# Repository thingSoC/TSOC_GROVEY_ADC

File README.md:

# TSOC_GROVEY_ADC - thingSoC ADS1115/ADS1015 ADC Module :

**TSOC_GROVEY_ADC** is a four(4) port Analog-to-Digital converter board, an Embedded Module for thingSoC.

The **TSOC_GROVEY_ADC** can operate at either 3.3V or 5V, and can also level translate 3.3V processor bus to 5V Analog peripherals when needed.

The **TSOC_GROVEY_ADC** allows you to connect [thingSoC](http://thingsoc.github.io/), [Mikrobus](http://www.mikroe.com/mikrobus/), 
and/or [Grove System](http://www.seeedstudio.com/blog/2016/03/09/tutorial-intro-to-grove-connectors-for-arduinoraspberry-pi-projects/) 
Modules all at the same time, with any processor module.
This gives you maximum flexiblity for sensor and actuator selection, and reuse. 
When populated with the ADS1115 device it provides 16 bit ADC conversion, and when populated with the ADS1015 device provides 12 bit ADC conversion.

The thingSoC "Grovey Series" was designed as "Everyday Electronics", a no-frills, low cost, approach to modular embedded product design.
thingSoC boards are similar in size to most break-out-boards (BOBs), but feature a standardized stacking pinout, as well as an I2C metadata store (EEPROM)
to indicate what peripherals are installed.

[TSOC_GROVEY_ADC](https://github.com/thingSoC/TSOC_GROVEY_ADC)

---------------------------------------

## TSOC_GROVEY_ADC Status <a name="TSOC_GROVEY_ADC_status"/>

**11/06/2016:** 
Revision 1.0 - Initial Layout released to OSHpark

**01/10/2017:**
Revison 2.0 - released to OSHpark

---------------------------------------
## TSOC_GROVEY_ADC Model Images

[TSOC_GROVEY_ADC](https://github.com/thingSoC/TSOC_GROVEY_ADC)

[TSOC_GROVEY_ADC](https://github.com/thingSoC/TSOC_GROVEY_ADC)

---------------------------------------

## TSOC_GROVEY_ADC Documentation Index <a name="TSOC_GROVEY_ADC_documentation_index"/>

[TSOC_GROVEY_ADC Project](http://thingsoc.github.io/projects/TSOC_GROVEY_ADC.html)

[TSOC_GROVEY_ADC Hardware](https://github.com/thingSoC/TSOC_GROVEY_ADC/tree/master/TSOC_GROVEY_ADC/hardware)

---------------------------------------

## thingSoC Documentation Index <a name="thingSoC_documentation_index"/>

[thingSoC Organization Website](http://thingSoC.github.io)

[thingSoC FAQ - Frequently Asked Questions](http://thingsoc.github.io/support/faq.html)

---------------------------------------

[ 
*thingSoC*](http://thingsoc.github.io)

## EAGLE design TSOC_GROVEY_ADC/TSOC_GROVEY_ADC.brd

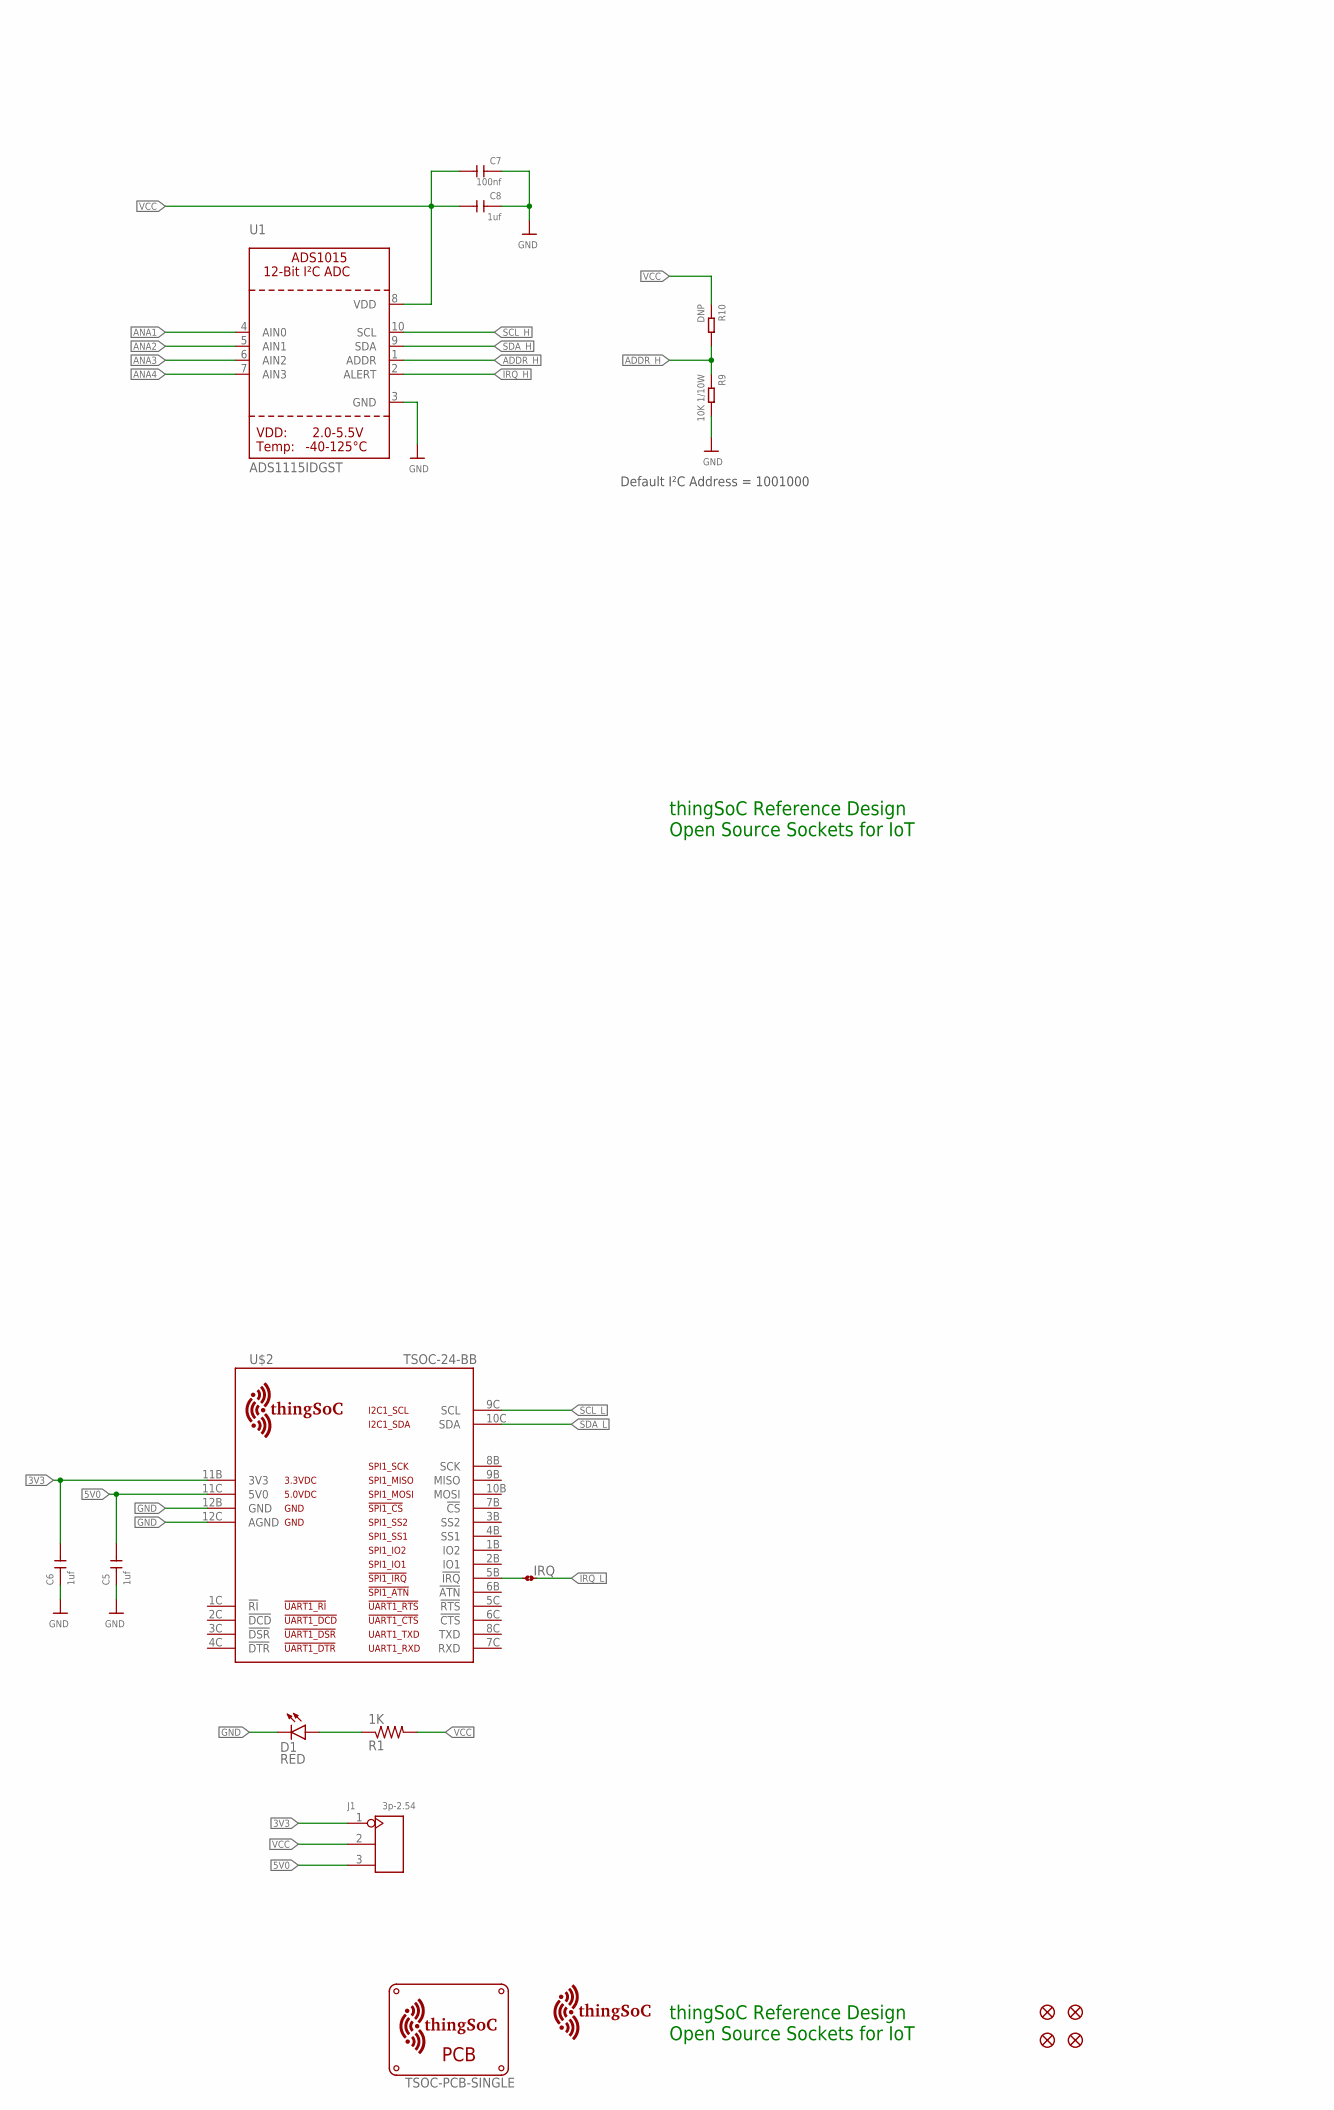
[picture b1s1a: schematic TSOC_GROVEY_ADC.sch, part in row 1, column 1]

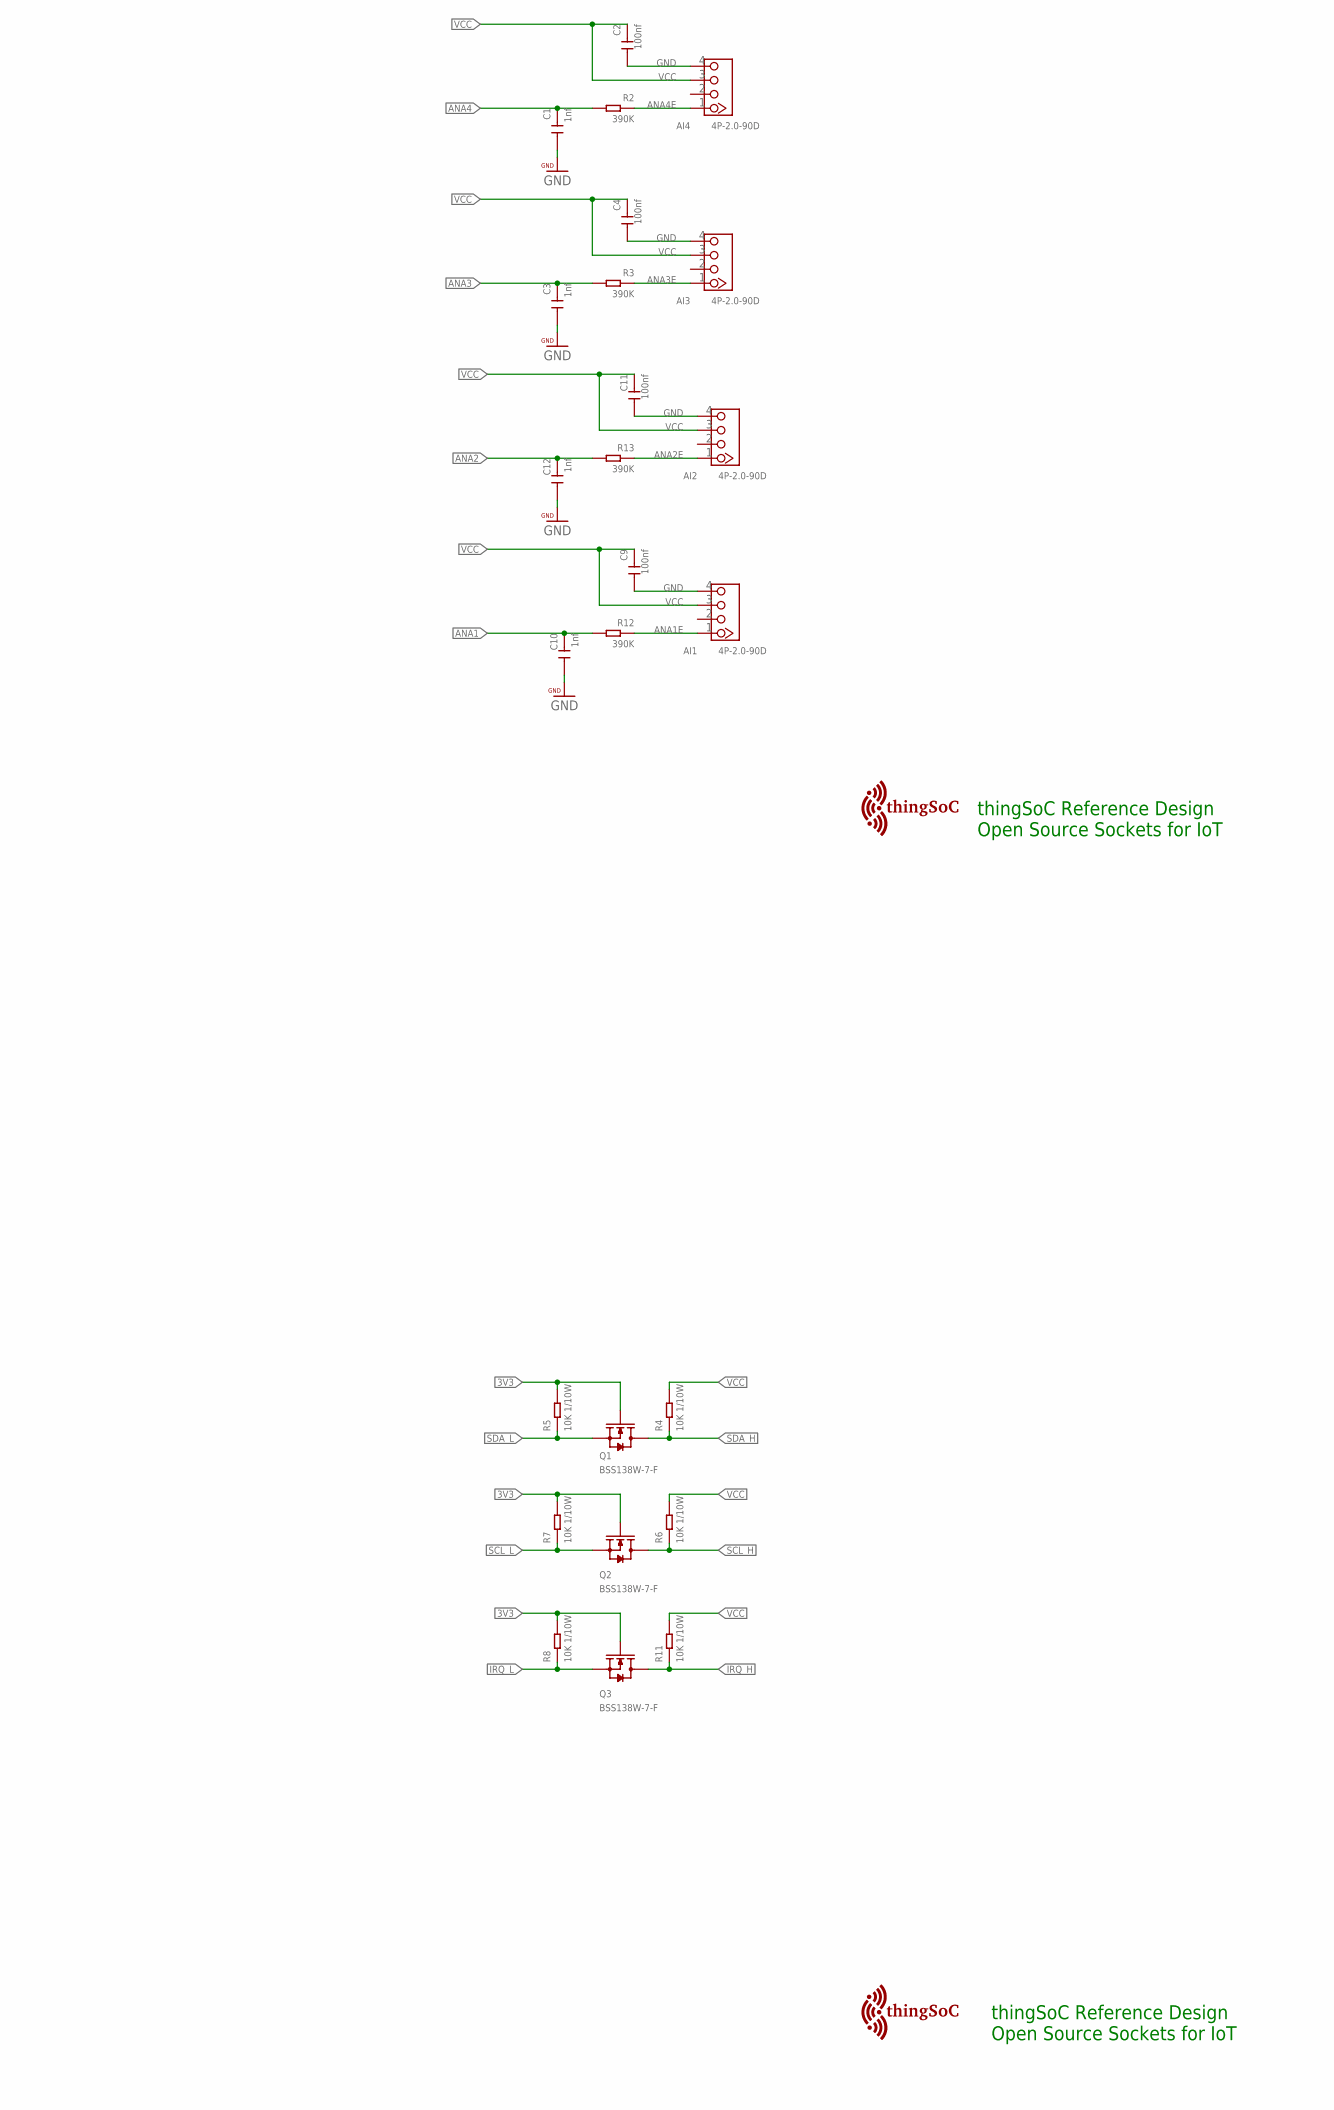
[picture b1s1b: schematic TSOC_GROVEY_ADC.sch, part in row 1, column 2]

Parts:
AI1, AI2, AI3, AI4: 4P-2.0-90D; HW4-2.0-90D
C1, C3, C10, C12: 1nf; C0603
C2, C4, C7, C9, C11: 100nf; C0603
C5, C6, C8: 1uf; C0603
D1: RED; LED-0603
FID1, FID2, FID3, FID4: FIDUCIALUFIDUCIAL; MICRO-FIDUCIAL
IRQ: JMP-2-NO
J1: 3p-2.54; H3-2.54
Q1, Q2, Q3: BSS138W-7-F; SOT-23
R1: 1K; 0603-RES
R2, R3, R12, R13: 390K; R0603
R4, R5, R6, R7, R8, R9, R11: 10K 1/10W; R0603
R10: DNP; R0603
U1: ADS1115IDGST; MSOP10
U$1: TSOC-PCB-SINGLE; TSOC-BB-BRD-DIM
U$2: TSOC-24-BB; TSOC-BB-S24
U$100, U$103: TSOC-LOGO-SMALL; TSOC-LOGO-SML
U$102: TSOC-LOGO-LRG

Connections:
3V3: C6.2, J1.1, Q1.1 (G), Q2.1 (G), Q3.1 (G), R5.2, R7.2, R8.2, U$2.11B (3V3)
5V0: C5.2, J1.3, U$2.11C (5V0)
ADDR_H: R9.1, R10.2, U1.1 (ADDR)
ANA1: C10.1, R12.2, U1.4 (AIN0)
ANA1E: AI1.1, R12.1
ANA2: C12.1, R13.2, U1.5 (AIN1)
ANA2E: AI2.1, R13.1
ANA3: C3.1, R3.2, U1.6 (AIN2)
ANA3E: AI3.1, R3.1
ANA4: C1.1, R2.2, U1.7 (AIN3)
ANA4E: AI4.1, R2.1
GND: AI1.4, AI2.4, AI3.4, AI4.4, C1.2, C2.2, C3.2, C4.2, C5.1, C6.1, C7.1, C8.1, C9.2, C10.2, C11.2, C12.2, D1.C, R9.2, U1.3 (GND), U$2.12B (GND), U$2.12C (AGND)
IRQE: IRQ.1, U$2.5B (!IRQ)
IRQ_H: Q3.3 (D), R11.1, U1.2 (ALERT)
IRQ_L: IRQ.2, Q3.2 (S), R8.1
unnamed: D1.A, R1.1
SCL_H: Q2.3 (D), R6.1, U1.10 (SCL)
SCL_L: Q2.2 (S), R7.1, U$2.9C (SCL)
SDA_H: Q1.3 (D), R4.1, U1.9 (SDA)
SDA_L: Q1.2 (S), R5.1, U$2.10C (SDA)
VCC: AI1.3, AI2.3, AI3.3, AI4.3, C2.1, C4.1, C7.2, C8.2, C9.1, C11.1, J1.2, R1.2, R4.2, R6.2, R10.1, R11.2, U1.8 (VDD)

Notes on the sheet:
thingSoC Reference Design Open Source Sockets for IoT
Default I²C Address = 1001000

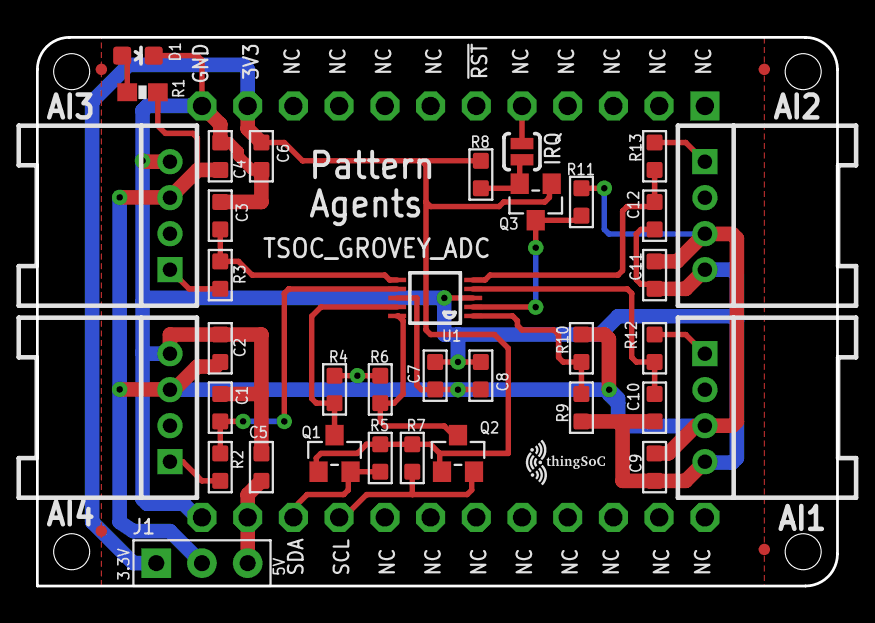
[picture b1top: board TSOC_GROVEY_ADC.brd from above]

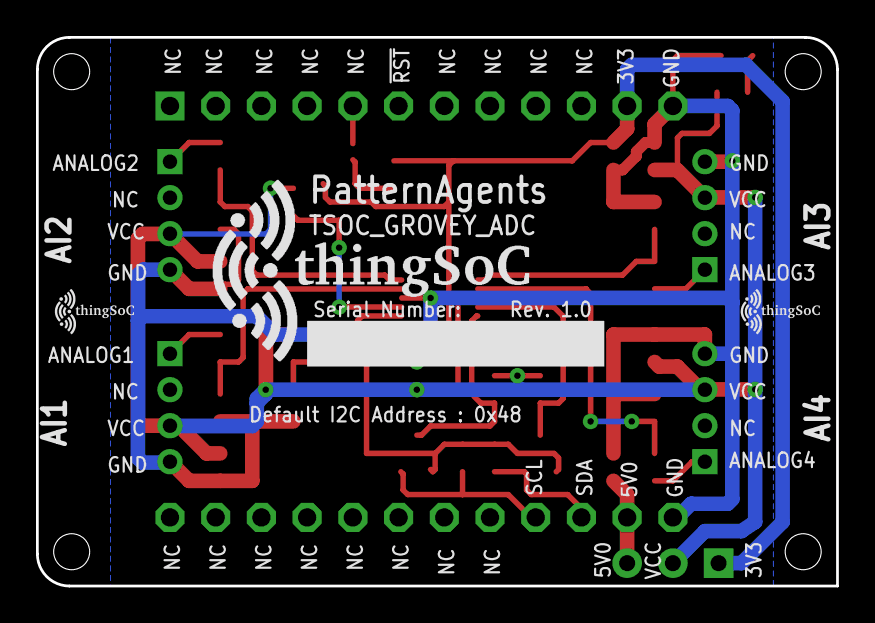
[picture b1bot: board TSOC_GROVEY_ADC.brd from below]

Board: 2 copper layers, 44.5 x 30.5 mm, 46 parts (3 on the bottom side), 21 nets.

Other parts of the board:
U$101: TSOC-LOGO-SMALL; TSOC-LOGO-SML

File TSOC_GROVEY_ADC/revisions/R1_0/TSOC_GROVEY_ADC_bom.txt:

Partlist exported from 
U:/PatternAgents/eagle/TSOC_Modules/TSOC_GROVEY_ADC/TSOC_GROVEY_ADC/revisions/R1_0/TSOC_GROVEY_ADC.sch at 1/29/2017 11:52:49 AM

Qty Value             Device                             Package         Parts                       Description                                          
1   RED               LED0603                            LED-0603        D1                          LEDs                                                 
1   ADS1115IDGST      ADC_ADS1015                        MSOP10          U1                          ADS1015 12-bit 4-Channel I2C ADC
3   BSS138W-7-F       SMD-MOSFET-N-CH-50V-200MA-BSS138W  SOT-23          Q1, Q2, Q3                  305030000                                            
1   1K                RESISTOR_SFE0603-RES               0603-RES        R1                          Resistor                                             
7   10K 1/10W         SMD-RES-10K-5%-1/10W(0603)         R0603           R4, R5, R6, R7, R8, R9, R11 301010293                                            
4   390K              SMD-RES-150K-1%-1/10W(0603)        R0603           R2, R3, R12, R13            301010205                                            
5   100nf             CERAMIC-100NF-50V-10%-X7R(0603)    C0603           C2, C4, C7, C9, C11         302010138                                            
4   1nf               CERAMIC-1NF-50V-5%-C0G(0603)       C0603           C1, C3, C10, C12            302010341                                            
3   1uf               CERAMIC-1UF-25V-10%-X7R(0603)      C0603           C5, C6, C8                  302010139                                            
1   3p-2.54           DIP-BLACK-MALE-HEADER-VERT         H3-2.54         J1                          320020079                                            
4   4P-2.0-90D        GROVE-CONNECTOR-DIP-90D(4P-2.0)    HW4-2.0-90D     AI1, AI2, AI3, AI4          320110034                                            
1                     JMP-2-NO                           JMP-2-NO        IRQ                         Two Terminal Jumper - Normally Open
----------------------------------------------------------------------------
1   DNP               SMD-RES-10K-5%-1/10W(0603)         R0603           R10                         301010293

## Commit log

2017-02-10 verson 2.0
2017-02-10 version 2.0
2017-02-28 update docs

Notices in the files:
parts and their libraries:
thingSoC: License : http://creativecommons.org/licenses/by-sa/4.0
(Creative Commons 4.0)
PatternAgents-Beautify: License : http://creativecommons.org/licenses/by-sa/3.0
(Creative Commons 3.0)
